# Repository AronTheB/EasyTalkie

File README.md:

# A ESP32/ESPNOW based walkie talkie

## Description

This is a easy to build/use Walkie-Talkie, that work via the ESPNOW system. The project uses a ESP-32 S3, INMP441, MAX98357A, SSD1306 OLED SCREEN, and 1000mAH LIPO BATTERY.

Made for [fallout.hackclub.com](https://fallout.hackclub.com/)

### WHY I MADE THIS:

I made this project, beaceuse my mom always have to yell at me to hear that she is calling me. So i made this walkie talkie so we can communicate easier in the house. I think also anyone could use this for easy communication and also at event like fallout where there are hunderds of kids, and you need to quickly communicate something to your partner.

### HOW TO BUILD:

You can replicate this project at home pretty easily. Clone this repo and download all the neccesary files such as the gerber.zip for pcb .stp files for the 3d models to print and also use the BOM to find all the parts needed for the project. After everything arrives solder it like in the schematic. (The battery has to be manually wired as shown in the schematic, the gnd of the battery should be connected to the gnd pin on the xiao via wires), put the pcb in the case, it should fit like a glove. connect it to a computer via a cable and flash the ESP32 with the firmware and after a reboot it should start working.

### HOW TO USE/FEATURES:

After turning on the ESP-32's will find eachother if near and than use the button to trasmit audio between the walkie-talkies. the main feature is the communication, if u press the button you start speaking while holding the button down, it will start transmitting audio and if you are not holding the key down, you can receive audio.

## KiCad

### Schematic

### PCB

## Fusion 360

## Preview

https://github.com/user-attachments/assets/4c29f206-930c-4e9f-b8dc-11138d7f1e36

## BOM
make this into a mk table

| NAME | LINK | PRICE | QUANTITY | Need To Buy? |
|------|------|-------|----------|--------------|
| XIAO ESP32 S3 | [AliExpress](https://www.aliexpress.com/item/1005005382287176.html) | $6.64 | 2 | Yes |
| INMP441 | [AliExpress](https://www.aliexpress.com/item/1005007987577953.html) | $1.39 | 2 | Yes |
| MAX98357A | [AliExpress](https://www.aliexpress.com/item/1005007003802663.html) | $1.63 | 2 | Yes |
| SSD1306 | [AliExpress](https://www.aliexpress.com/item/32896971385.html) | $1.85 | 2 | Yes |
| LiPo 1000mAh | [AliExpress](https://www.aliexpress.com/item/1005004375261361.html) | $7.69 | 2 | Yes |
| SS-12D00 6mm | [AliExpress](https://www.aliexpress.com/item/1005005633418066.html) | $1.77 | 2 | Yes |
| 8Ω 1W 28mm Speaker | [AliExpress](https://www.aliexpress.com/item/1005005458778825.html) | $0.42 | 2 | Yes |
| MX Switches | [AliExpress](https://www.aliexpress.com/item/1005004285423123.html) | $2.86 | 1 | Yes |
| Keycaps | [AliExpress](https://www.aliexpress.com/item/1005009364428646.html) | $3.54 | 1 | Yes |
| PCB | JLCPCB | $2.00 | 1 | Yes |
| 3D Print | JLC3DP | $6.33 | 1 | Yes |
| **TOTAL** | | **$57.51** | | |

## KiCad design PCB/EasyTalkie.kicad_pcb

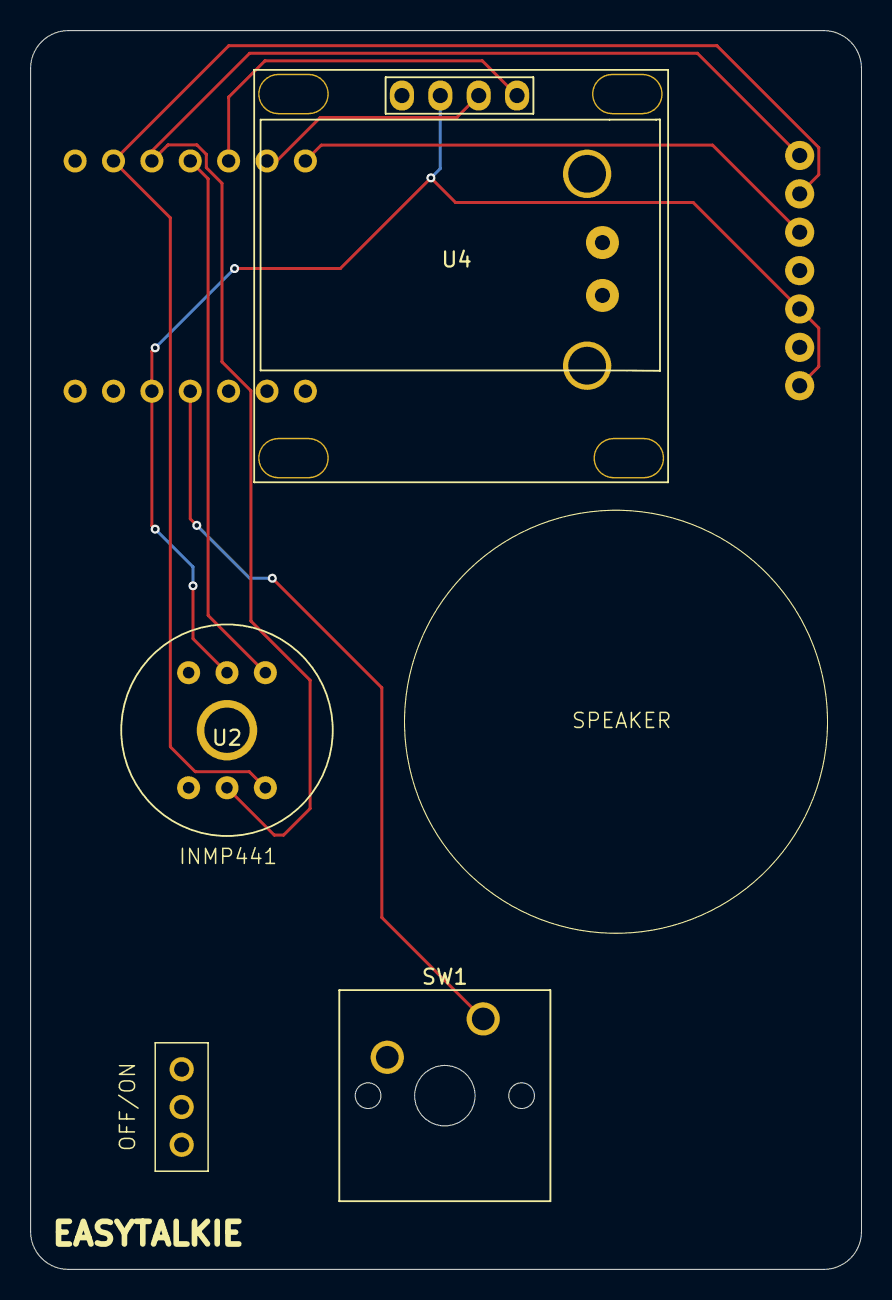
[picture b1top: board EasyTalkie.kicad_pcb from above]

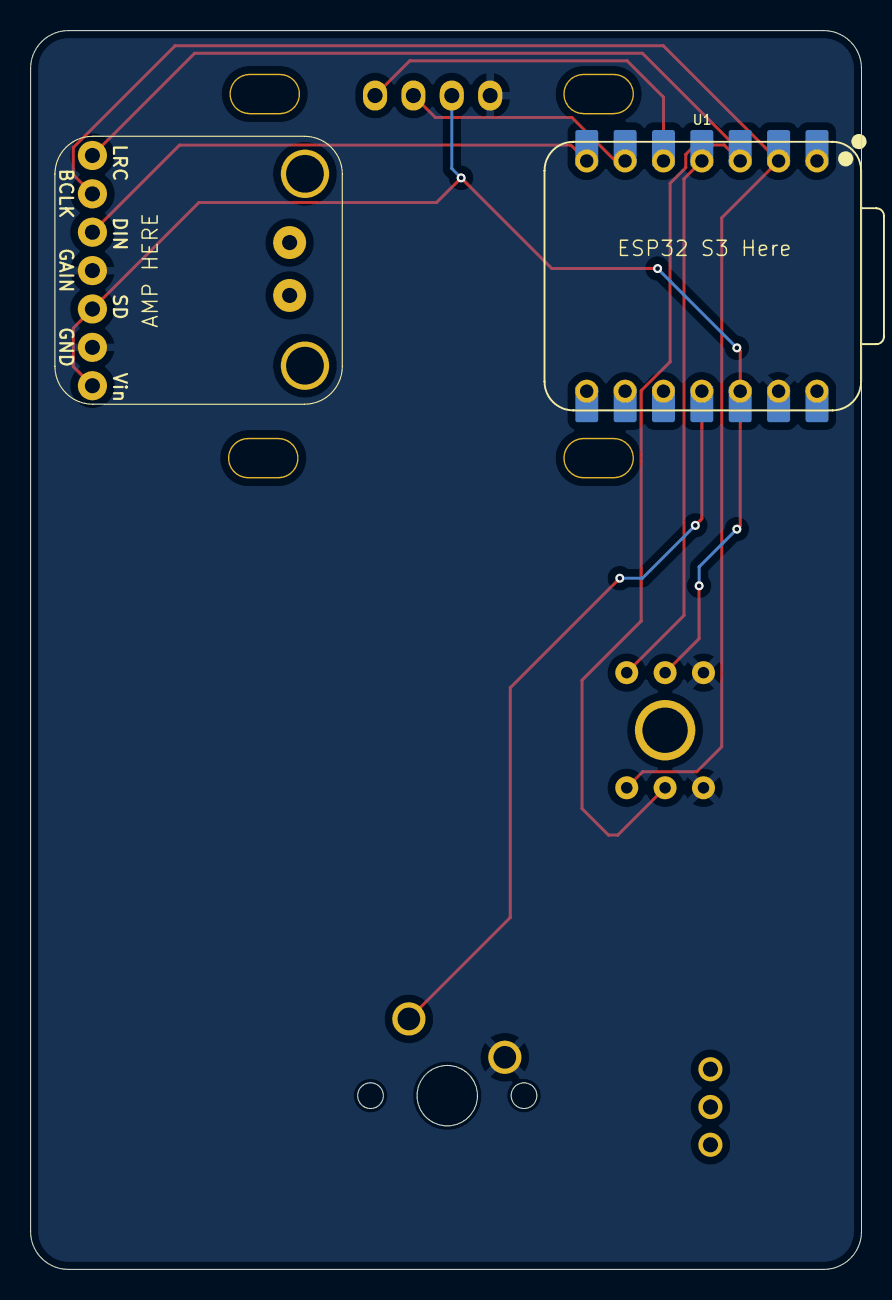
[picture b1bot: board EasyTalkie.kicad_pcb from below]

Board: 2 copper layers, 55.0 x 82.0 mm, 6 parts (2 on the bottom side), 9 nets.

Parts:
SW1: SW_Push; SW_Cherry_MX_1.00u_PCB
SW2: SS12D00
U1: XIAO-ESP32-S3-DIP
U2: INMP441; inmp441
U3: MAX98357A; MAX98357A Module
U4: SSD1306; 128x64OLED

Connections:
3V: U1.12 (3V3), U2.2 (VDD), U3.4 (~SD_MODE), U3.7 (VDD), U4.2 (VCC)
GND: SW1.2, U1.13 (GND), U2.1 (GND), U2.4 (L/R), U3.2 (GAIN_SLOT), U3.3 (GND), U4.1 (GND)
GPI02: U1.2 (GPIO2_A1_D1), U2.6 (SCK), U3.16 (BCLK)
GPI03: U1.3 (GPIO3_A2_D2), U2.5 (WS), U3.14 (LRCLK)
GPI04: U1.4 (GPIO4_A3_D3), U2.3 (SD)
GPI05: U1.5 (GPIO5_A4_D4_SDA), U4.4 (SDA)
GPI06: U1.6 (GPIO6_A5_D5_SCL), U4.3 (SCL)
GPI043: U1.7 (GPIO43_D6_TX), U3.1 (DIN)
unnamed: SW1.1, U1.11 (GPIO9_A10_D10_MOSI)

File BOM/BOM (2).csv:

NAME,LINK,PRICE,QUANTITY,Need To buy?
XIAO ESP32 S3,https://www.aliexpress.com/item/1005005382287176.html,"$6,64",2,Yes
INMP441,https://www.aliexpress.com/item/1005007987577953.html,"$1,39",2,Yes
MAX98357A,https://www.aliexpress.com/item/1005007003802663.html,"$1,63",2,Yes
SSD1306,"https://www.aliexpress.com/item/32896971385.html
","$1,85",2,Yes
LiPo 1000mAh,https://www.aliexpress.com/item/1005004375261361.html,"$7,69",2,Yes
SS-12D00 6mm,https://www.aliexpress.com/item/1005005633418066.html,"$1,77",2,Yes
8Ω 1W 28mm Speaker,https://www.aliexpress.com/item/1005005458778825.html,"$0,42",2,Yes
Mx Switches,https://www.aliexpress.com/item/1005004285423123.html,"$2,86",1,Yes
Keycaps,https://www.aliexpress.com/item/1005009364428646.html,"$3,54",1,Yes
TOTAL:,,"$49,18",,

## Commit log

2026-05-23 Enhance README with project details and images
    Added a project description and images for schematic, PCB, and Fusion 360.
2026-05-23 Update project title to include ESPNOW
2026-05-23 Update README with project description and usage
    Clarify functionality of the walkie-talkie project and improve grammar.
2026-06-02 animation
2026-06-02 fix animation
2026-06-02 Add preview section to README
2026-06-05 firmware
2026-06-05 Add BOM section with component details to README
    Added a Bill of Materials (BOM) section with details on components, links, prices, and quantities.
2026-06-05 Update README with project replication instructions
    Added instructions for replicating the project at home, including cloning the repo, downloading necessary files, and flashing the ESP32.
2026-06-05 zine
2026-06-05 Rename EASYTALKIE.csv to BOM.csv
2026-06-06 Fix typos and enhance README content
    Corrected typos and improved clarity in the README.
2026-06-09 Update README with clearer project instructions
    Clarified instructions on using the walkie-talkie project and improved grammar.
2026-06-09 Enhance README formatting and fix typos
    Updated README.md to improve formatting and correct typos.
2026-06-09 Improve build instructions in README.md
    Updated instructions for building the project to include fitting the PCB in the case and connecting it to a computer for flashing.
2026-06-12 Enhance project description in README.md
    Expanded the project description to include additional use cases for the walkie talkie, emphasizing its utility in crowded events.
2026-06-19 Update README with detailed battery wiring instructions
    Clarified battery wiring instructions in the build section of the README.
